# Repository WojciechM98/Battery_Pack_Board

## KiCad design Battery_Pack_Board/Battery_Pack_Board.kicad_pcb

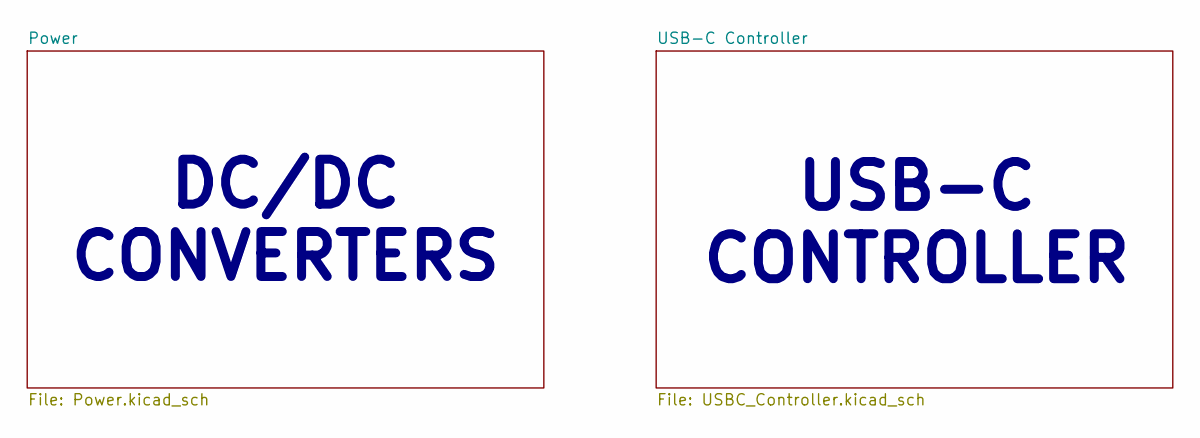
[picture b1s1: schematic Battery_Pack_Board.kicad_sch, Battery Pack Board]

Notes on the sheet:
DC/DC CONVERTERS
USB-C CONTROLLER

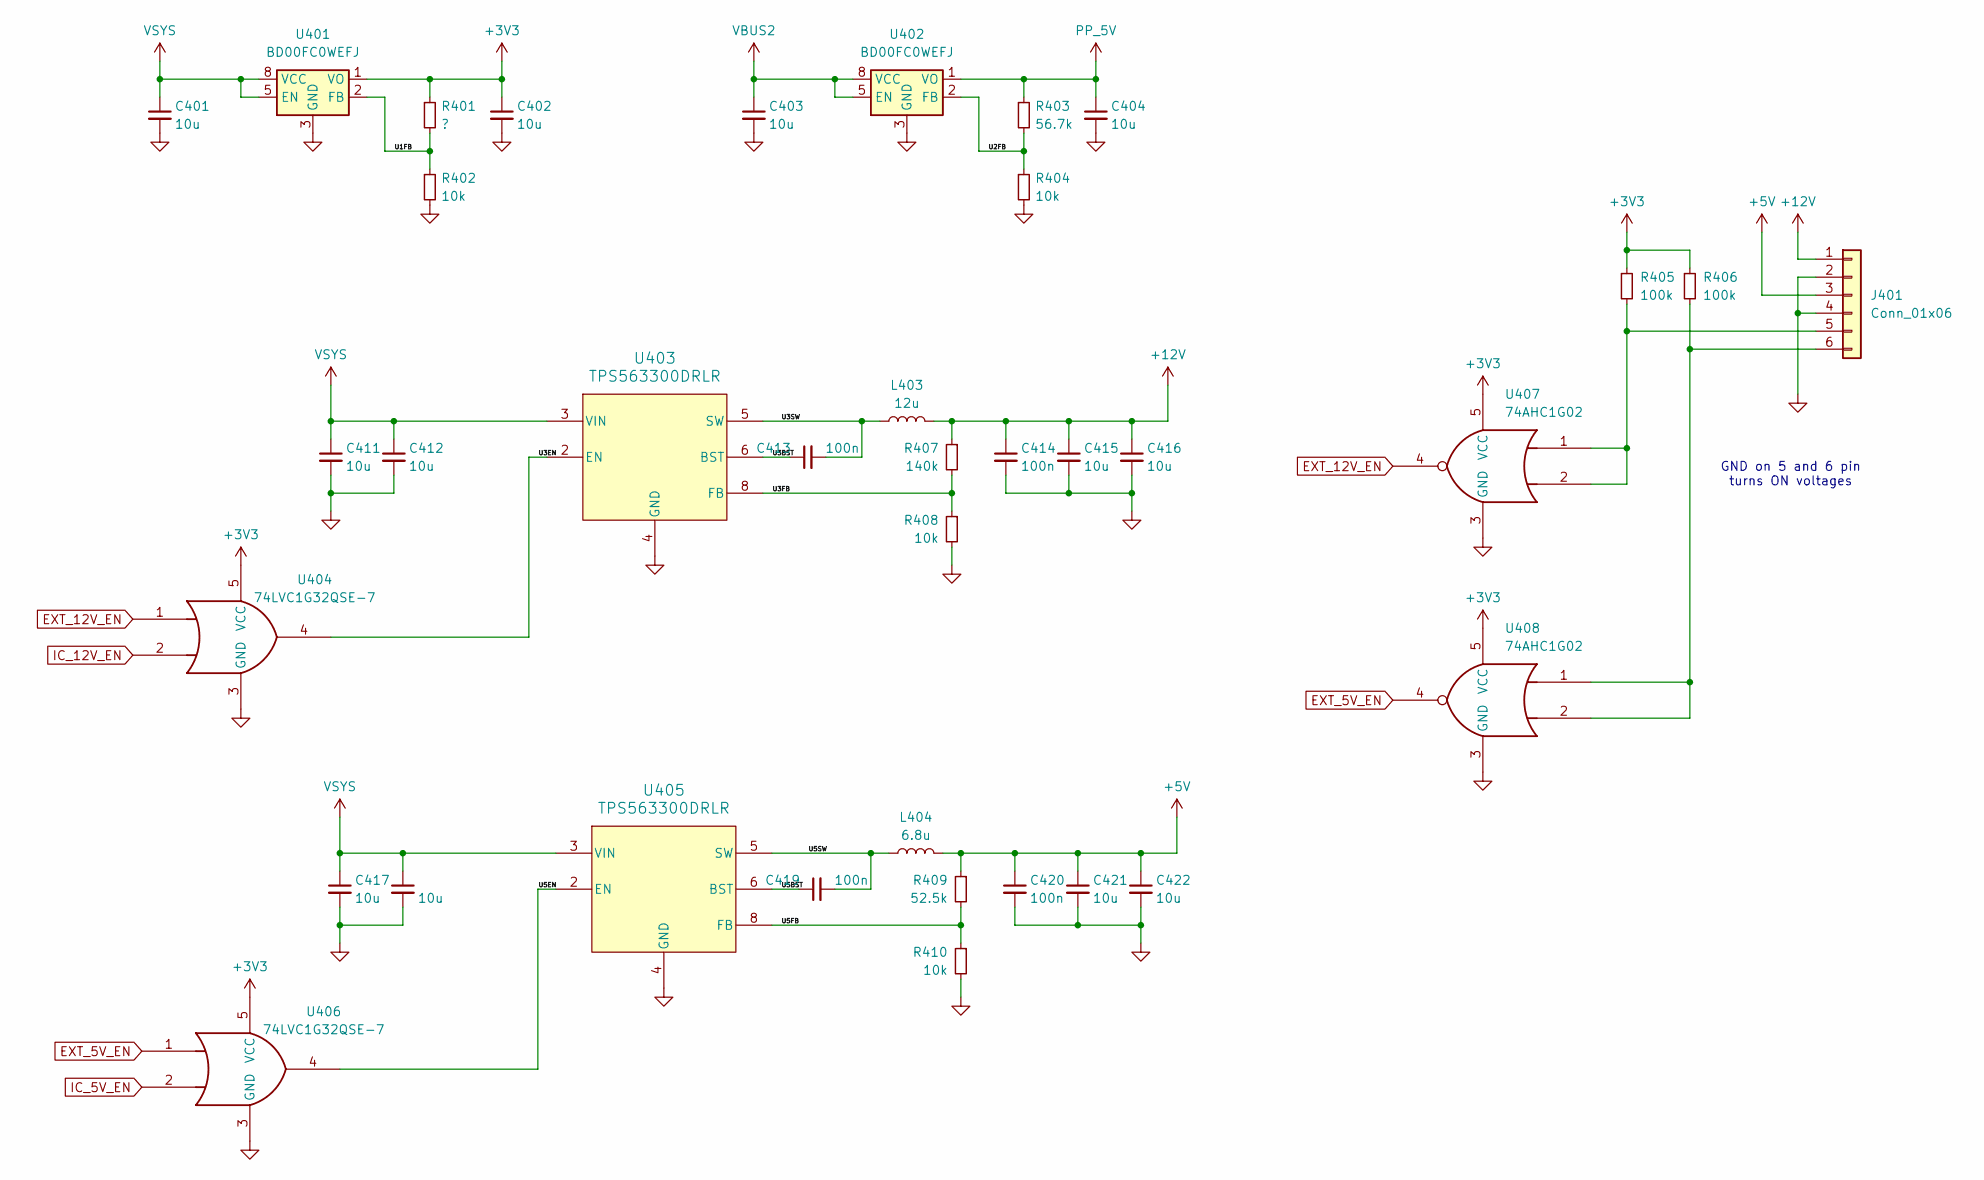
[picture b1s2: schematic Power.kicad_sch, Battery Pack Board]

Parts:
C401, C402, C403, C404, C411, C412, C415, C416, C417, C418, C421, C422: 10u; C_1206_3216Metric
C413, C414, C419, C420: 100n; C_0402_1005Metric
J401: Conn_01x06; 436500600
L403: 12u; SRR1050A
L404: 6.8u; SRP4020TA
R401: ?; R_0402_1005Metric
R402, R404, R408, R410: 10k; R_0402_1005Metric
R403: 56.7k; R_0402_1005Metric
R405, R406: 100k; R_0402_1005Metric
R407: 140k; R_0402_1005Metric
R409: 52.5k; R_0402_1005Metric
U401, U402: BD00FC0WEFJ; HTSOP-8-1EP_3.9x4.9mm_P1.27mm_EP2.4x3.2mm
U403, U405: TPS563300DRLR; SOT583_DRL
U404, U406: 74LVC1G32QSE-7; SOT65P210X110-5N_SOT-353
U407, U408: 74AHC1G02; SOT65P210X110-5N_SOT-353

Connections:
+3V3: C402.1, R401.1, R405.1, R406.1, U401.1 (VO), U404.5 (VCC), U406.5 (VCC), U407.5 (VCC), U408.5 (VCC); also elsewhere on the board
+5V: C420.1, C421.1, C422.1, J401.3, L404.2, R409.1; also elsewhere on the board
+12V: C414.1, C415.1, C416.1, J401.1, L403.2, R407.1; also elsewhere on the board
/Power/U1FB: R401.2, R402.1, U401.2 (FB)
/Power/U2FB: R403.2, R404.1, U402.2 (FB)
/Power/U3BST: C413.1, U403.6 (BST)
/Power/U3EN: U403.2 (EN), U404.4
/Power/U3FB: R407.2, R408.1, U403.8 (FB)
/Power/U3SW: C413.2, L403.1, U403.5 (SW)
/Power/U5BST: C419.1, U405.6 (BST)
/Power/U5EN: U405.2 (EN), U406.4
/Power/U5FB: R409.2, R410.1, U405.8 (FB)
/Power/U5SW: C419.2, L404.1, U405.5 (SW)
EXT_5V_EN: U406.1, U408.4
EXT_12V_EN: U404.1, U407.4
GND: C401.2, C402.2, C403.2, C404.2, C411.2, C412.2, C414.2, C415.2, C416.2, C417.2, C418.2, C420.2, C421.2, C422.2, J401.2, J401.4, R402.2, R404.2, R408.2, R410.2, U401.3 (GND), U401.9 (GND), U402.3 (GND), U402.9 (GND), U403.4 (GND), U404.3 (GND), U405.4 (GND), U406.3 (GND), U407.3 (GND), U408.3 (GND); also elsewhere on the board
IC_5V_EN: U406.2; also elsewhere on the board
IC_12V_EN: U404.2; also elsewhere on the board
unnamed: J401.5, R405.2, U407.1, U407.2
unnamed: J401.6, R406.2, U408.1, U408.2
PP_5V: C404.1, R403.1, U402.1 (VO); also elsewhere on the board
VBUS2: C403.1, U402.5 (EN), U402.8 (VCC); also elsewhere on the board
VSYS: C401.1, C411.1, C412.1, C417.1, C418.1, U401.5 (EN), U401.8 (VCC), U403.3 (VIN), U405.3 (VIN); also elsewhere on the board

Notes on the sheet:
GND on 5 and 6 pin turns ON voltages

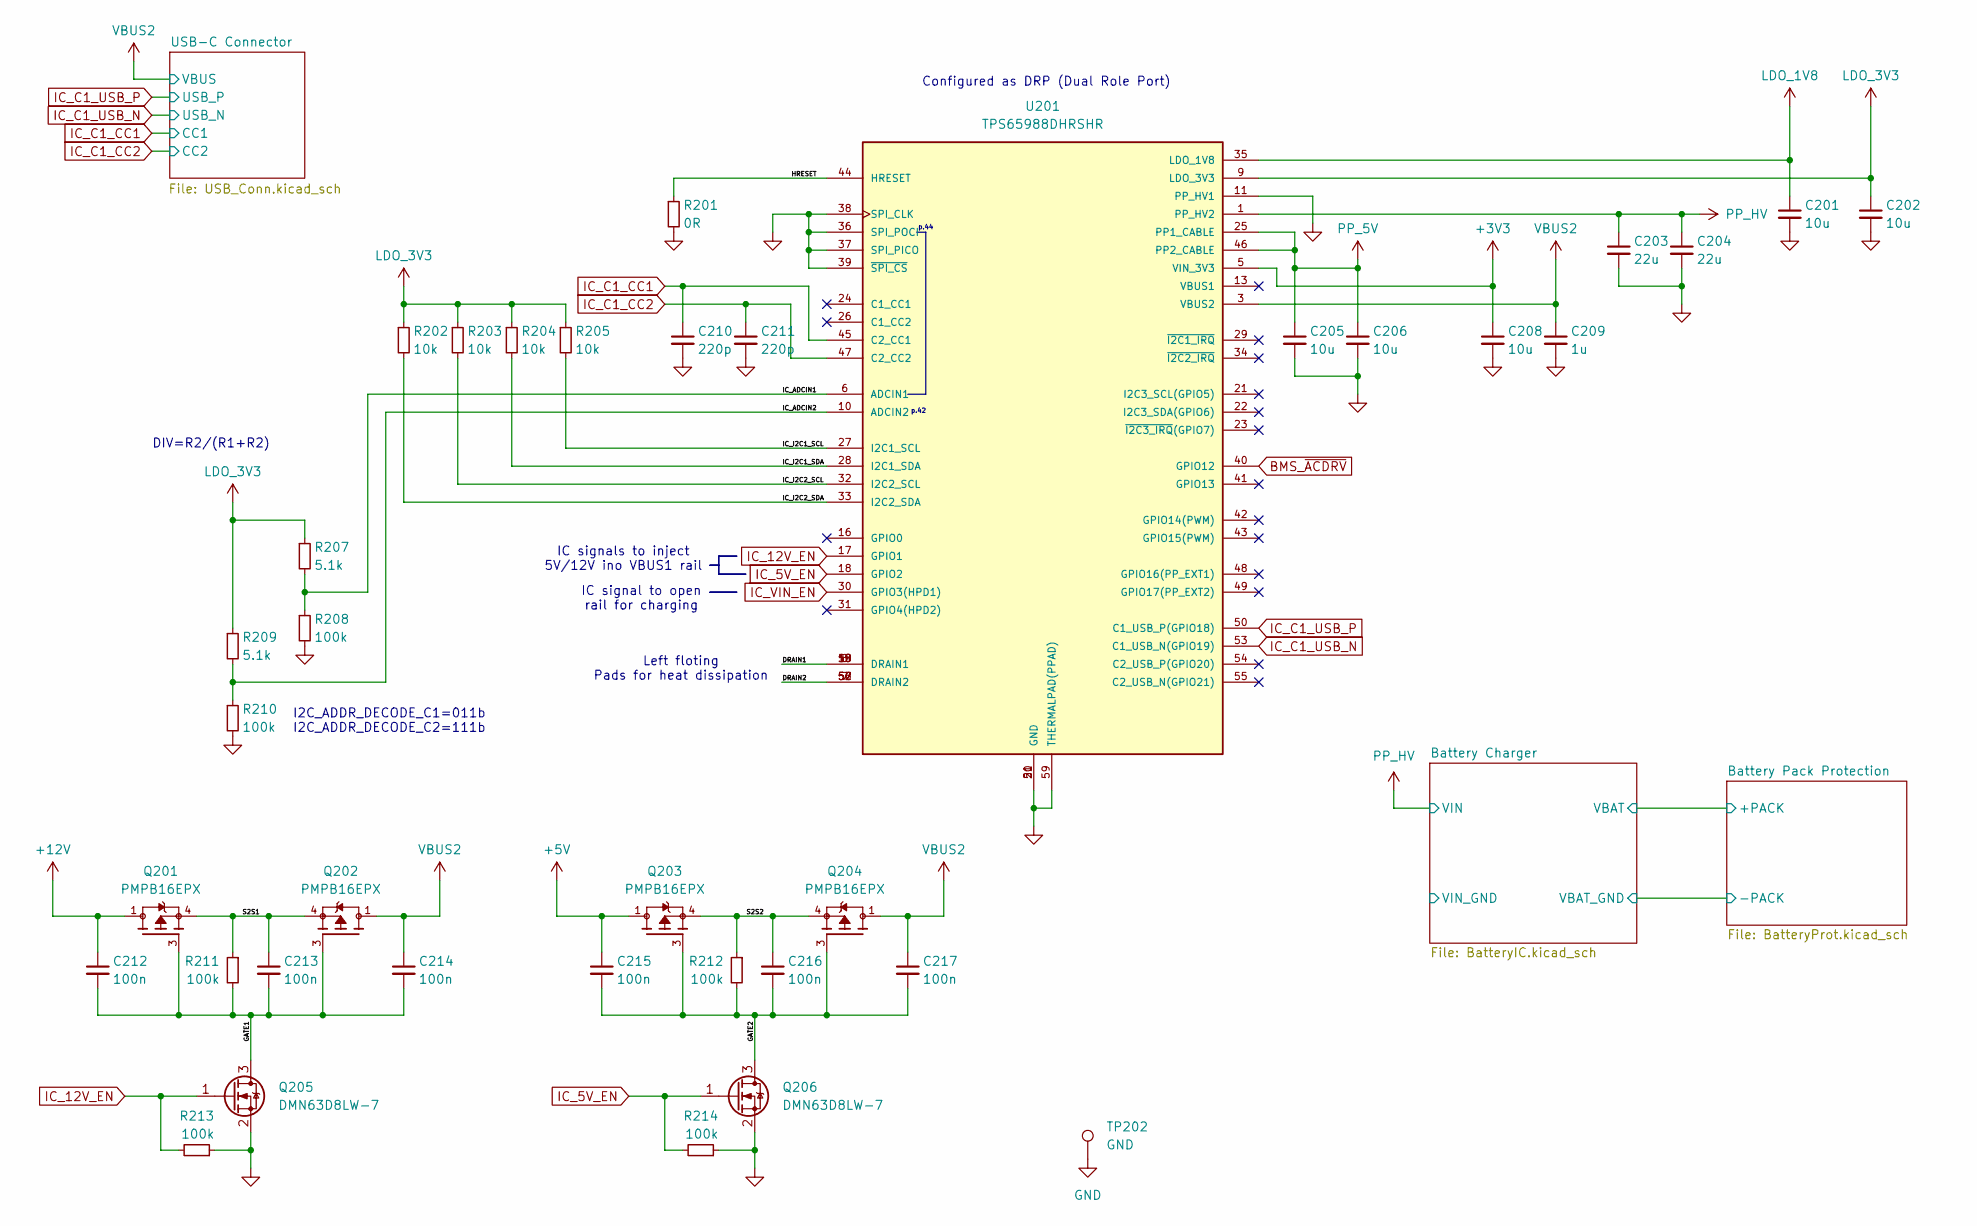
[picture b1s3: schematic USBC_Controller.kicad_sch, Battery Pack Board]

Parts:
C201, C202, C205, C206, C208: 10u; C_0402_1005Metric
C203, C204: 22u; C_0603_1608Metric
C209: 1u; C_0603_1608Metric
C210, C211: 220p; C_0402_1005Metric
C212, C213, C214, C215, C216, C217: 100n; C_0402_1005Metric
Q201, Q202, Q203, Q204: PMPB16EPX; PARTREV v.1
Q205, Q206: DMN63D8LW-7; SOT-323_SC-70
R201: 0R; R_0402_1005Metric
R202, R203, R204, R205: 10k; R_0402_1005Metric
R207, R209: 5.1k; R_0402_1005Metric
R208, R210, R211, R212, R213, R214: 100k; R_0402_1005Metric
TP202: GND; TestPoint_Pad_D2.0mm
U201: TPS65988DHRSHR; PARTREV AUGUST 2021

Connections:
+3V3: C208.1, U201.5 (VIN_3V3); also elsewhere on the board
+5V: C215.1, Q203.1, Q203.2, Q203.5, Q203.6, Q203.7; also elsewhere on the board
+12V: C212.1, Q201.1, Q201.2, Q201.5, Q201.6, Q201.7; also elsewhere on the board
/USB-C Controller/DRAIN1: U201.8 (DRAIN1), U201.15 (DRAIN1), U201.19 (DRAIN1), U201.58 (DRAIN1)
/USB-C Controller/DRAIN2: U201.7 (DRAIN2), U201.52 (DRAIN2), U201.56 (DRAIN2), U201.57 (DRAIN2)
/USB-C Controller/GATE1: C212.2, C213.2, C214.2, Q201.3, Q202.3, Q205.3 (D), R211.2
/USB-C Controller/GATE2: C215.2, C216.2, C217.2, Q203.3, Q204.3, Q206.3 (D), R212.2
/USB-C Controller/HRESET: R201.1, U201.44 (HRESET)
/USB-C Controller/IC_ADCIN1: R207.2, R208.1, U201.6 (ADCIN1)
/USB-C Controller/IC_ADCIN2: R209.2, R210.1, U201.10 (ADCIN2)
/USB-C Controller/IC_I2C1_SCL: R205.2, U201.27 (I2C1_SCL)
/USB-C Controller/IC_I2C1_SDA: R204.2, U201.28 (I2C1_SDA)
/USB-C Controller/IC_I2C2_SCL: R203.2, U201.32 (I2C2_SCL)
/USB-C Controller/IC_I2C2_SDA: R202.2, U201.33 (I2C2_SDA)
/USB-C Controller/S2S1: C213.1, Q201.4, Q201.8, Q202.4, Q202.8, R211.1
/USB-C Controller/S2S2: C216.1, Q203.4, Q203.8, Q204.4, Q204.8, R212.1
BMS_~ACDRV: U201.40 (GPIO12); also elsewhere on the board
GND: C201.2, C202.2, C203.2, C204.2, C205.2, C206.2, C208.2, C209.2, C210.2, C211.2, Q205.2 (S), Q206.2 (S), R201.2, R208.2, R210.2, R213.1, R214.1, TP202.1, U201.11 (PP_HV1), U201.12 (PP_HV1), U201.20 (GND), U201.36 (SPI_POCI), U201.37 (SPI_PICO), U201.38 (SPI_CLK), U201.39 (~SPI_CS), U201.51 (GND), U201.59 (THERMALPAD(PPAD)); also elsewhere on the board
IC_5V_EN: Q206.1 (G), R214.2, U201.18 (GPIO2); also elsewhere on the board
IC_12V_EN: Q205.1 (G), R213.2, U201.17 (GPIO1); also elsewhere on the board
IC_C1_CC1: C210.1, U201.45 (C2_CC1); also elsewhere on the board
IC_C1_CC2: C211.1, U201.47 (C2_CC2); also elsewhere on the board
IC_C1_USB_N: U201.53 (C1_USB_N(GPIO19)); also elsewhere on the board
IC_C1_USB_P: U201.50 (C1_USB_P(GPIO18)); also elsewhere on the board
IC_VIN_EN: U201.30 (GPIO3(HPD1)); also elsewhere on the board
LDO_1V8: C201.1, U201.35 (LDO_1V8)
LDO_3V3: C202.1, R202.1, R203.1, R204.1, R205.1, R207.1, R209.1, U201.9 (LDO_3V3)
PP_5V: C205.1, C206.1, U201.25 (PP1_CABLE), U201.46 (PP2_CABLE); also elsewhere on the board
PP_HV: C203.1, C204.1, U201.1 (PP_HV2), U201.2 (PP_HV2); also elsewhere on the board
VBUS2: C209.1, C214.1, C217.1, Q202.1, Q202.2, Q202.5, Q202.6, Q202.7, Q204.1, Q204.2, Q204.5, Q204.6, Q204.7, U201.3 (VBUS2), U201.4 (VBUS2); also elsewhere on the board

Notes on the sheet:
Left floting Pads for heat dissipation
DIV=R2/(R1+R2)
p.44
IC signals to inject 5V/12V ino VBUS1 rail
Configured as DRP (Dual Role Port)
p.42
IC signal to open rail for charging
I2C_ADDR_DECODE_C1=011b I2C_ADDR_DECODE_C2=111b

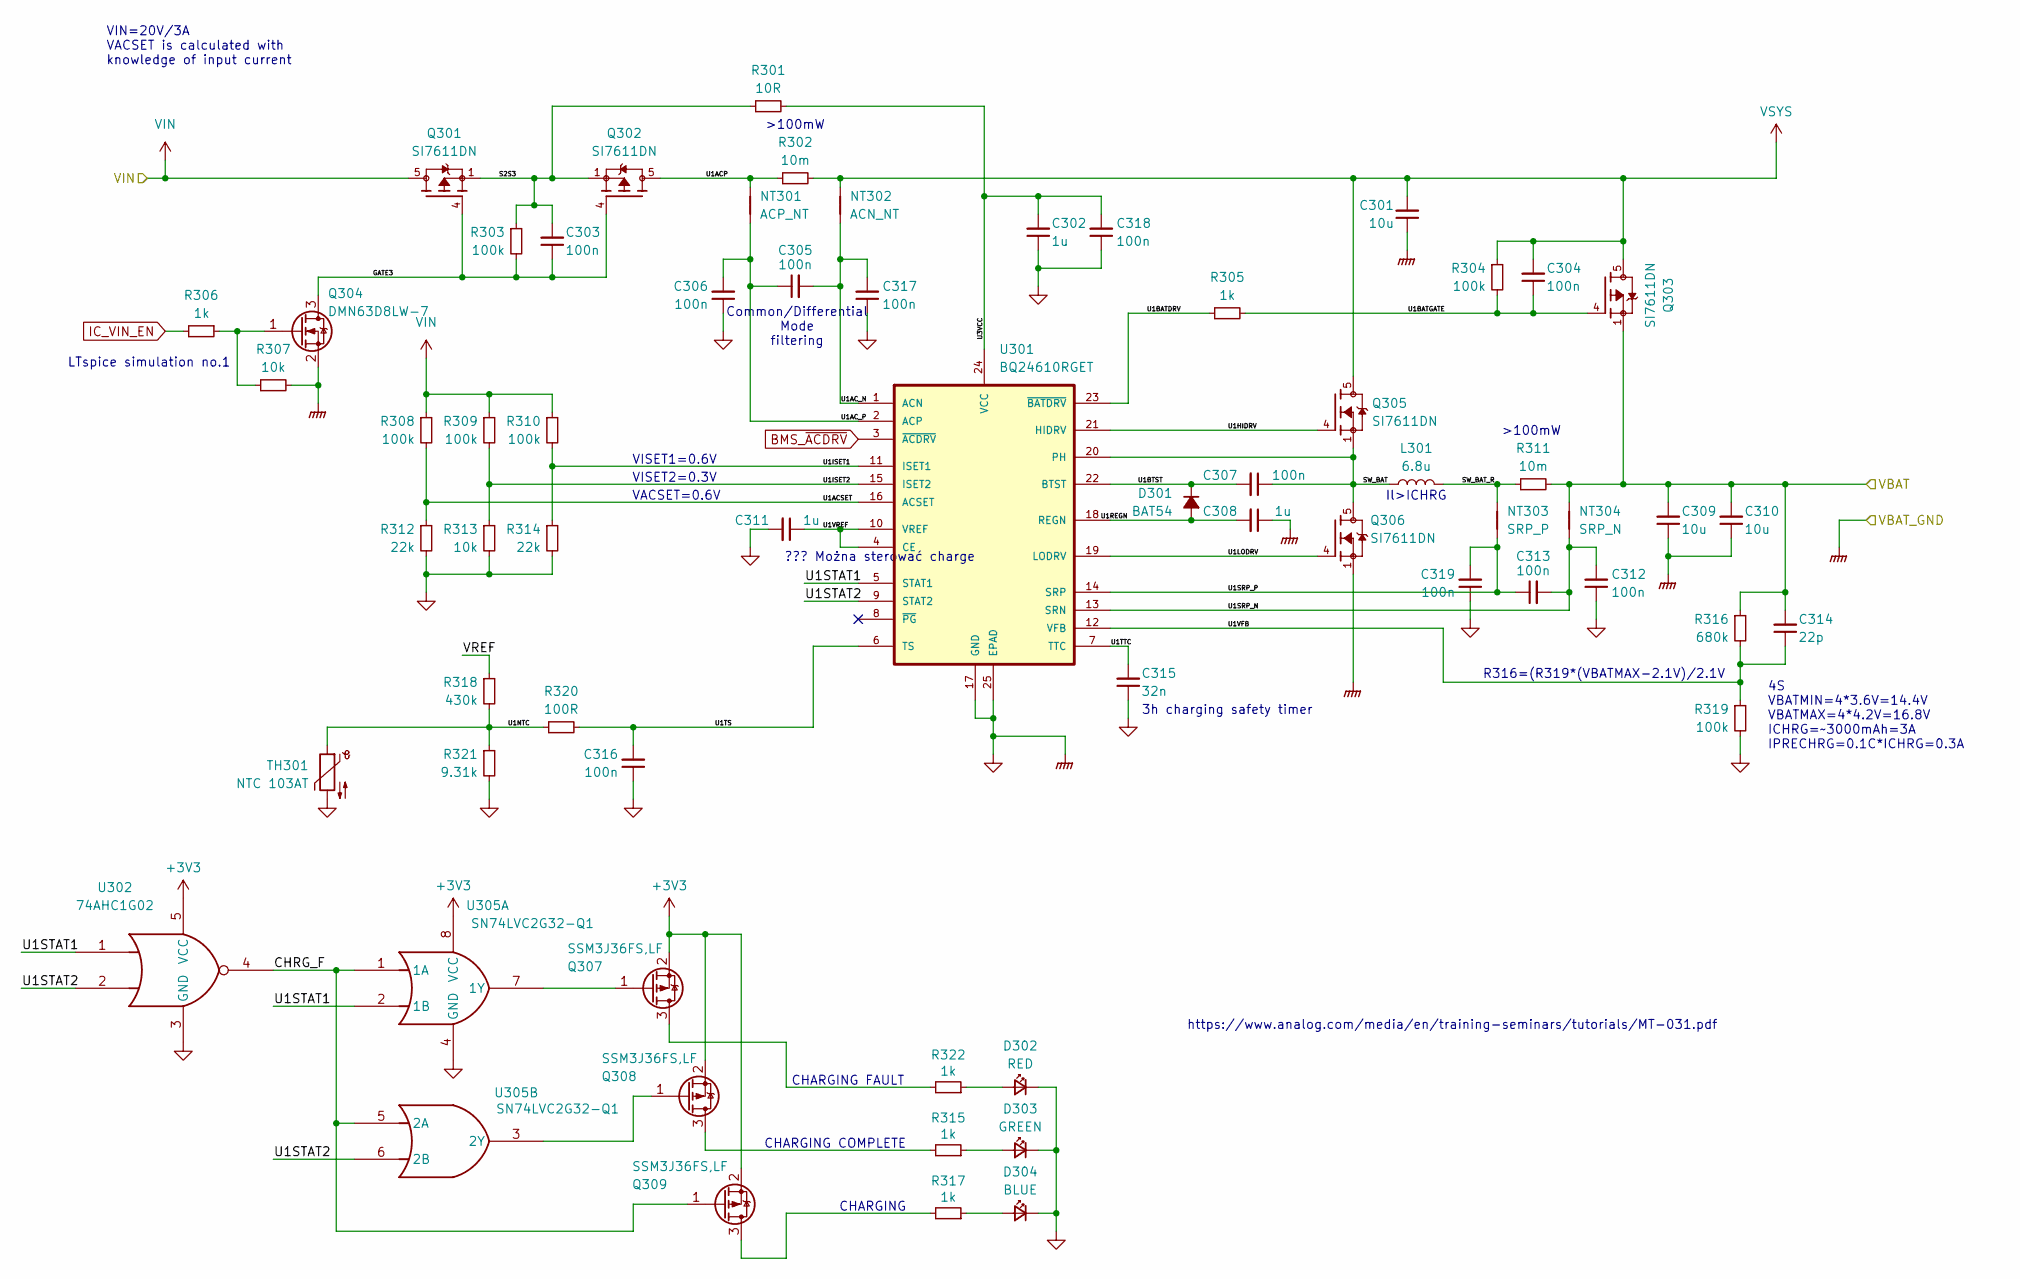
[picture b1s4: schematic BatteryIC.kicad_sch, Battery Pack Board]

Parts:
C301, C309, C310: 10u; C_1206_3216Metric
C302, C308, C311: 1u; C_0402_1005Metric
C303, C304, C305, C306, C307, C312, C313, C316, C317, C318, C319: 100n; C_0402_1005Metric
C314: 22p; C_0402_1005Metric
C315: 32n; C_0402_1005Metric
D301: BAT54; D_SOD-323F
D302: RED; LED_0603_1608Metric
D303: GREEN; LED_0603_1608Metric
D304: BLUE; LED_0603_1608Metric
L301: 6.8u; SRP4020TA
NT301: ACP_NT; NetTie_2_0,2mm
NT302: ACN_NT; NetTie_2_0,2mm
NT303: SRP_P; NetTie_2_0,2mm
NT304: SRP_N; NetTie_2_0,2mm
Q301, Q302, Q303: SI7611DN; VISHAY_SIS468DN-T1-GE3_SI7611DN-T1-GE3; PARTREV B
Q304: DMN63D8LW-7; SOT-323_SC-70
Q305, Q306: SI7611DN; VISHAY_SIS468DN-T1-GE3_SIS412DN-T1-GE3; PARTREV B
Q307, Q308, Q309: SSM3J36FS,LF; SOT-416
R301: 10R; R_0402_1005Metric
R302, R311: 10m; R_0805_2012Metric
R303, R304, R308, R309, R310, R319: 100k; R_0402_1005Metric
R305, R306, R315, R317, R322: 1k; R_0402_1005Metric
R307, R313: 10k; R_0402_1005Metric
R312, R314: 22k; R_0402_1005Metric
R316: 680k; R_0402_1005Metric
R318: 430k; R_0402_1005Metric
R320: 100R; R_0402_1005Metric
R321: 9.31k; R_0402_1005Metric
TH301: NTC 103AT; NTC_103AT
U301: BQ24610RGET; QFN50P400X400X100-25N
U302: 74AHC1G02; SOT65P210X110-5N_SOT-353
U305: SN74LVC2G32-Q1; SN74LVC2G32QDCURQ1

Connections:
+3V3: Q307.2 (S), Q308.2 (S), Q309.2 (S), U302.5 (VCC), U305.8 (VCC); also elsewhere on the board
/USB-C Controller/Battery Charger/CHRG_F: Q309.1 (G), U302.4, U305.1 (1A), U305.5 (2A)
/USB-C Controller/Battery Charger/GATE3: C303.1, Q301.4, Q302.4, Q304.3 (D), R303.2
/USB-C Controller/Battery Charger/S2S3: C303.2, Q301.1, Q301.2, Q301.3, Q302.1, Q302.2, Q302.3, R301.1, R303.1
/USB-C Controller/Battery Charger/SW_BAT: C307.1, L301.1, Q305.1, Q305.2, Q305.3, Q306.5, Q306.6, Q306.7, Q306.8, Q306.9, U301.20 (PH)
/USB-C Controller/Battery Charger/SW_BAT_R: L301.2, NT303.2, R311.1
/USB-C Controller/Battery Charger/U1ACP: NT301.2, Q302.5, Q302.6, Q302.7, Q302.8, Q302.9, R302.1
/USB-C Controller/Battery Charger/U1ACSET: R308.2, R312.1, U301.16 (ACSET)
/USB-C Controller/Battery Charger/U1AC_N: C305.2, C317.2, NT302.1, U301.1 (ACN)
/USB-C Controller/Battery Charger/U1AC_P: C305.1, C306.2, NT301.1, U301.2 (ACP)
/USB-C Controller/Battery Charger/U1BATDRV: R305.1, U301.23 (~BATDRV)
/USB-C Controller/Battery Charger/U1BATGATE: C304.1, Q303.4, R304.2, R305.2
/USB-C Controller/Battery Charger/U1BTST: C307.2, D301.1 (K), U301.22 (BTST)
/USB-C Controller/Battery Charger/U1HIDRV: Q305.4, U301.21 (HIDRV)
/USB-C Controller/Battery Charger/U1ISET1: R310.2, R314.1, U301.11 (ISET1)
/USB-C Controller/Battery Charger/U1ISET2: R309.2, R313.1, U301.15 (ISET2)
/USB-C Controller/Battery Charger/U1LODRV: Q306.4, U301.19 (LODRV)
/USB-C Controller/Battery Charger/U1NTC: R318.2, R320.1, R321.1, TH301.1
/USB-C Controller/Battery Charger/U1REGN: C308.2, D301.2 (A), U301.18 (REGN)
/USB-C Controller/Battery Charger/U1SRP_N: C312.2, C313.2, NT304.1, U301.13 (SRN)
/USB-C Controller/Battery Charger/U1SRP_P: C313.1, C319.2, NT303.1, U301.14 (SRP)
/USB-C Controller/Battery Charger/U1STAT1: U301.5 (STAT1), U302.1, U305.2 (1B)
/USB-C Controller/Battery Charger/U1STAT2: U301.9 (STAT2), U302.2, U305.6 (2B)
/USB-C Controller/Battery Charger/U1TS: C316.2, R320.2, U301.6 (TS)
/USB-C Controller/Battery Charger/U1TTC: C315.2, U301.7 (TTC)
/USB-C Controller/Battery Charger/U1VFB: C314.1, R316.2, R319.1, U301.12 (VFB)
/USB-C Controller/Battery Charger/U1VREF: C311.1, U301.4 (CE), U301.10 (VREF)
/USB-C Controller/Battery Charger/U3VCC: C302.2, C318.2, R301.2, U301.24 (VCC)
/USB-C Controller/Battery Charger/VBAT: C309.2, C310.2, C314.2, NT304.2, Q303.1, Q303.2, Q303.3, R311.2, R316.1; also elsewhere on the board
/USB-C Controller/Battery Charger/VREF: R318.1
BMS_~ACDRV: U301.3 (~ACDRV); also elsewhere on the board
GND: C301.1, C302.1, C306.1, C308.1, C309.1, C310.1, C311.2, C312.1, C315.1, C316.1, C317.1, C318.1, C319.1, D302.1 (K), D303.1 (K), D304.1 (K), Q304.2 (S), Q306.1, Q306.2, Q306.3, R307.2, R312.2, R313.2, R314.2, R319.2, R321.2, TH301.2, U301.17 (GND), U301.25 (EPAD), U302.3 (GND), U305.4 (GND); also elsewhere on the board
IC_VIN_EN: R306.2; also elsewhere on the board
unnamed: D302.2 (A), R322.1
unnamed: D303.2 (A), R315.1
unnamed: D304.2 (A), R317.1
unnamed: Q304.1 (G), R306.1, R307.1
unnamed: Q307.3 (D), R322.2
unnamed: Q307.1 (G), U305.7 (1Y)
unnamed: Q308.3 (D), R315.2
unnamed: Q308.1 (G), U305.3 (2Y)
unnamed: Q309.3 (D), R317.2
PP_HV: Q301.5, Q301.6, Q301.7, Q301.8, Q301.9, R308.1, R309.1, R310.1; also elsewhere on the board
VSYS: C301.2, C304.2, NT302.2, Q303.5, Q303.6, Q303.7, Q303.8, Q303.9, Q305.5, Q305.6, Q305.7, Q305.8, Q305.9, R302.2, R304.1; also elsewhere on the board

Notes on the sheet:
VISET2=0.3V
??? Można sterować charge
Il>ICHRG
>100mW
https://www.analog.com/media/en/training-seminars/tutorials/MT-031.pdf
3h charging safety timer
VISET1=0.6V
Common/Differential Mode filtering
LTspice simulation no.1
CHARGING COMPLETE
R316=(R319*(VBATMAX-2.1V)/2.1V
VIN=20V/3A VACSET is calculated with knowledge of input current
CHARGING
VACSET=0.6V
4S VBATMIN=4*3.6V=14.4V VBATMAX=4*4.2V=16.8V ICHRG=~3000mAh=3A IPRECHRG=0.1C*ICHRG=0.3A
CHARGING FAULT

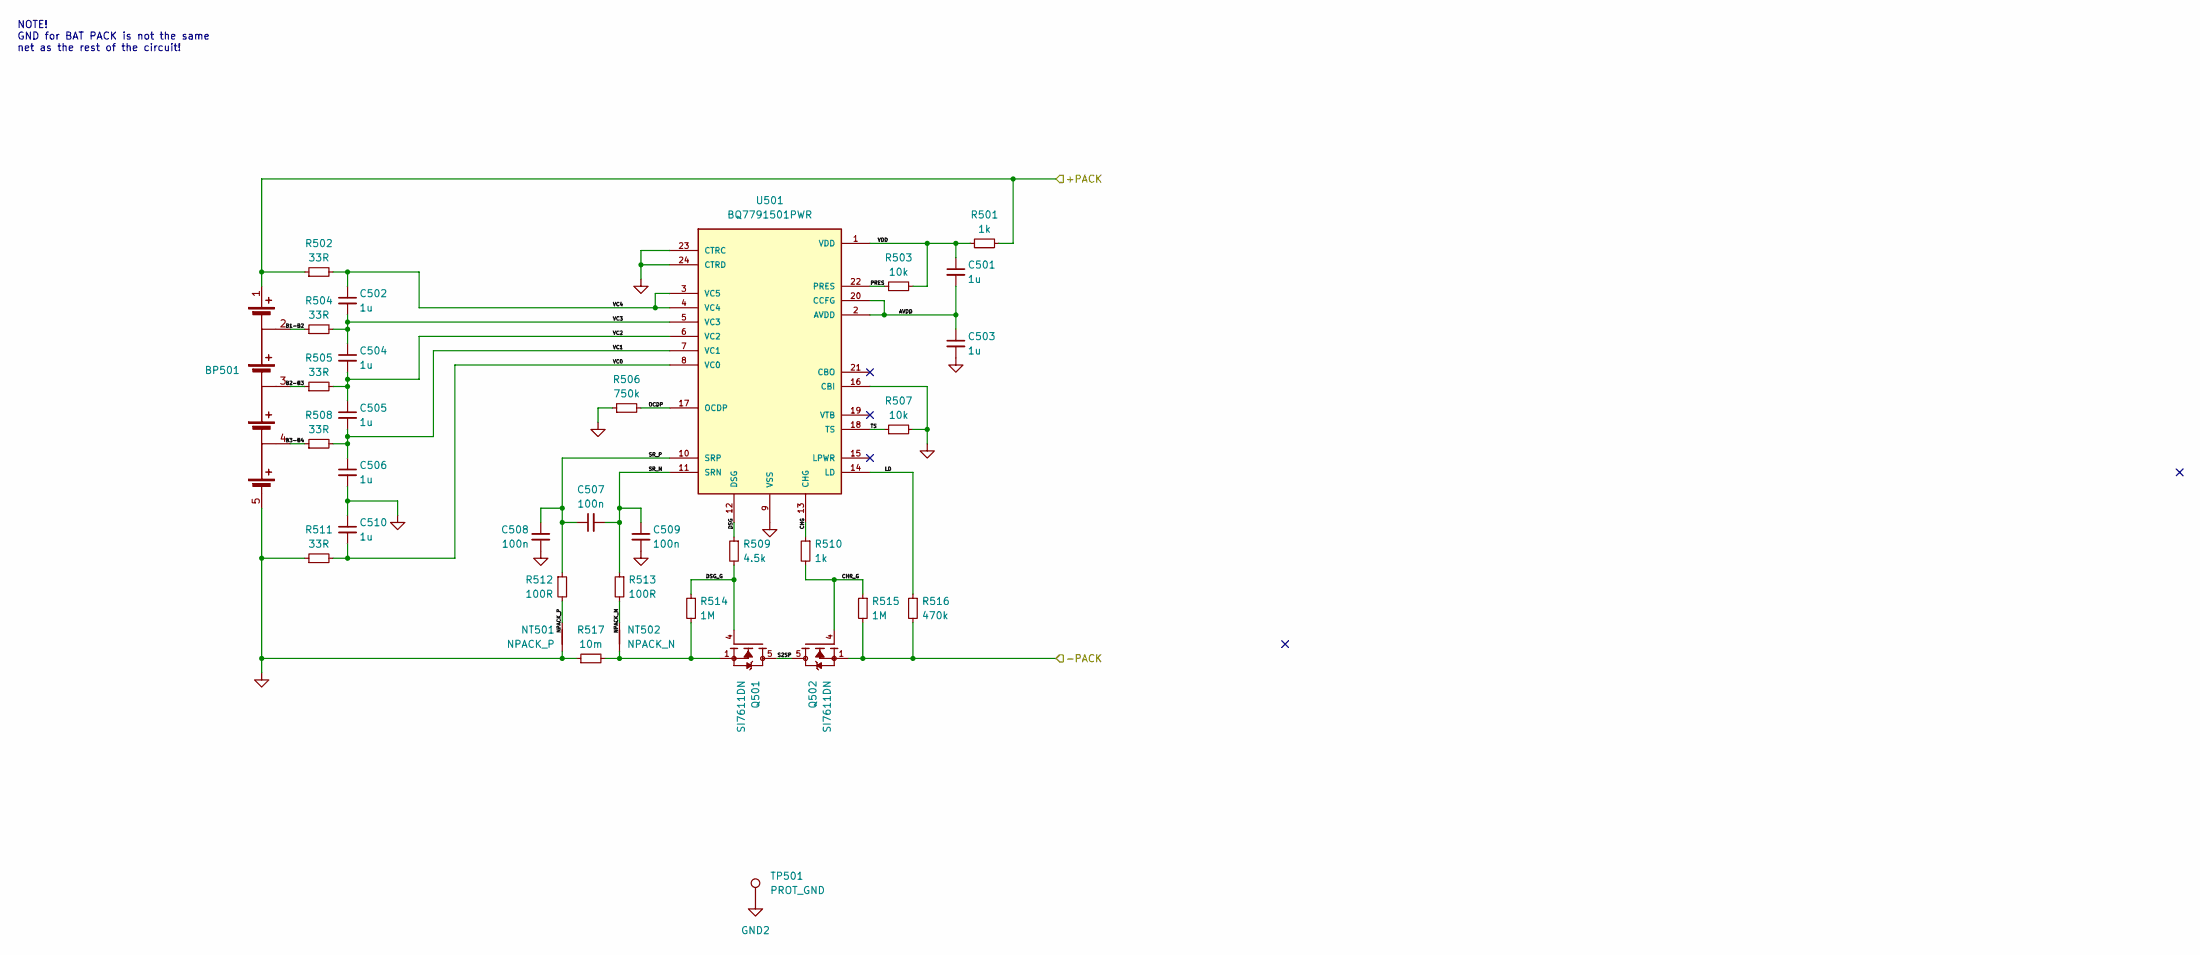
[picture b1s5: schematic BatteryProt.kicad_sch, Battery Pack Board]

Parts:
BP501: BatPack_4S
C501, C502, C503, C504, C505, C506, C510: 1u; C_0402_1005Metric
C507, C508, C509: 100n; C_0402_1005Metric
NT501: NPACK_P; NetTie_2_0,2mm
NT502: NPACK_N; NetTie_2_0,2mm
Q501, Q502: SI7611DN; VISHAY_SIS468DN-T1-GE3_SIS412DN-T1-GE3; PARTREV B
R501, R510: 1k; R_0402_1005Metric
R502, R504, R505, R508, R511: 33R; R_0402_1005Metric
R503, R507: 10k; R_0402_1005Metric
R506: 750k; R_0402_1005Metric
R509: 4.5k; R_0402_1005Metric
R512, R513: 100R; R_0402_1005Metric
R514, R515: 1M; R_0402_1005Metric
R516: 470k; R_0402_1005Metric
R517: 10m; R_0805_2012Metric
TP501: PROT_GND; TestPoint_Pad_D2.0mm
U501: BQ7791501PWR; SOP65P640X120-24N_BQ7791501PWR; PARTREV H

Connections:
/USB-C Controller/Battery Charger/VBAT: BP501.1, R501.2, R502.1; also elsewhere on the board
/USB-C Controller/Battery Pack Protection/AVDD: C501.2, C503.1, U501.2 (AVDD), U501.20 (CCFG)
/USB-C Controller/Battery Pack Protection/B1-B2: BP501.2, R504.1
/USB-C Controller/Battery Pack Protection/B2-B3: BP501.3, R505.1
/USB-C Controller/Battery Pack Protection/B3-B4: BP501.4, R508.1
/USB-C Controller/Battery Pack Protection/CHG: R510.1, U501.13 (CHG)
/USB-C Controller/Battery Pack Protection/CHR_G: Q502.4, R510.2, R515.1
/USB-C Controller/Battery Pack Protection/DSG: R509.1, U501.12 (DSG)
/USB-C Controller/Battery Pack Protection/DSG_G: Q501.4, R509.2, R514.1
/USB-C Controller/Battery Pack Protection/LD: R516.1, U501.14 (LD)
/USB-C Controller/Battery Pack Protection/NPACK_N: NT502.2, R513.2
/USB-C Controller/Battery Pack Protection/NPACK_P: NT501.2, R512.2
/USB-C Controller/Battery Pack Protection/OCDP: R506.2, U501.17 (OCDP)
/USB-C Controller/Battery Pack Protection/PRES: R503.1, U501.22 (PRES)
/USB-C Controller/Battery Pack Protection/S2SP: Q501.5, Q501.6, Q501.7, Q501.8, Q501.9, Q502.5, Q502.6, Q502.7, Q502.8, Q502.9
/USB-C Controller/Battery Pack Protection/SR_N: C507.2, C509.1, R513.1, U501.11 (SRN)
/USB-C Controller/Battery Pack Protection/SR_P: C507.1, C508.1, R512.1, U501.10 (SRP)
/USB-C Controller/Battery Pack Protection/TS: R507.1, U501.18 (TS)
/USB-C Controller/Battery Pack Protection/VC0: C510.2, R511.2, U501.8 (VC0)
/USB-C Controller/Battery Pack Protection/VC1: C505.2, C506.1, R508.2, U501.7 (VC1)
/USB-C Controller/Battery Pack Protection/VC2: C504.2, C505.1, R505.2, U501.6 (VC2)
/USB-C Controller/Battery Pack Protection/VC3: C502.2, C504.1, R504.2, U501.5 (VC3)
/USB-C Controller/Battery Pack Protection/VC4: C502.1, R502.2, U501.3 (VC5), U501.4 (VC4)
/USB-C Controller/Battery Pack Protection/VDD: C501.1, R501.1, R503.2, U501.1 (VDD)
GND: Q502.1, Q502.2, Q502.3, R515.2, R516.2; also elsewhere on the board
GND2: BP501.5, C503.2, C506.2, C508.2, C509.2, C510.1, NT501.1, R506.1, R507.2, R511.1, R517.1, TP501.1, U501.9 (VSS), U501.16 (CBI), U501.23 (CTRC), U501.24 (CTRD)
unnamed: NT502.1, Q501.1, Q501.2, Q501.3, R514.2, R517.2

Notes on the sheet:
NOTE! GND for BAT PACK is not the same net as the rest of the circuit!

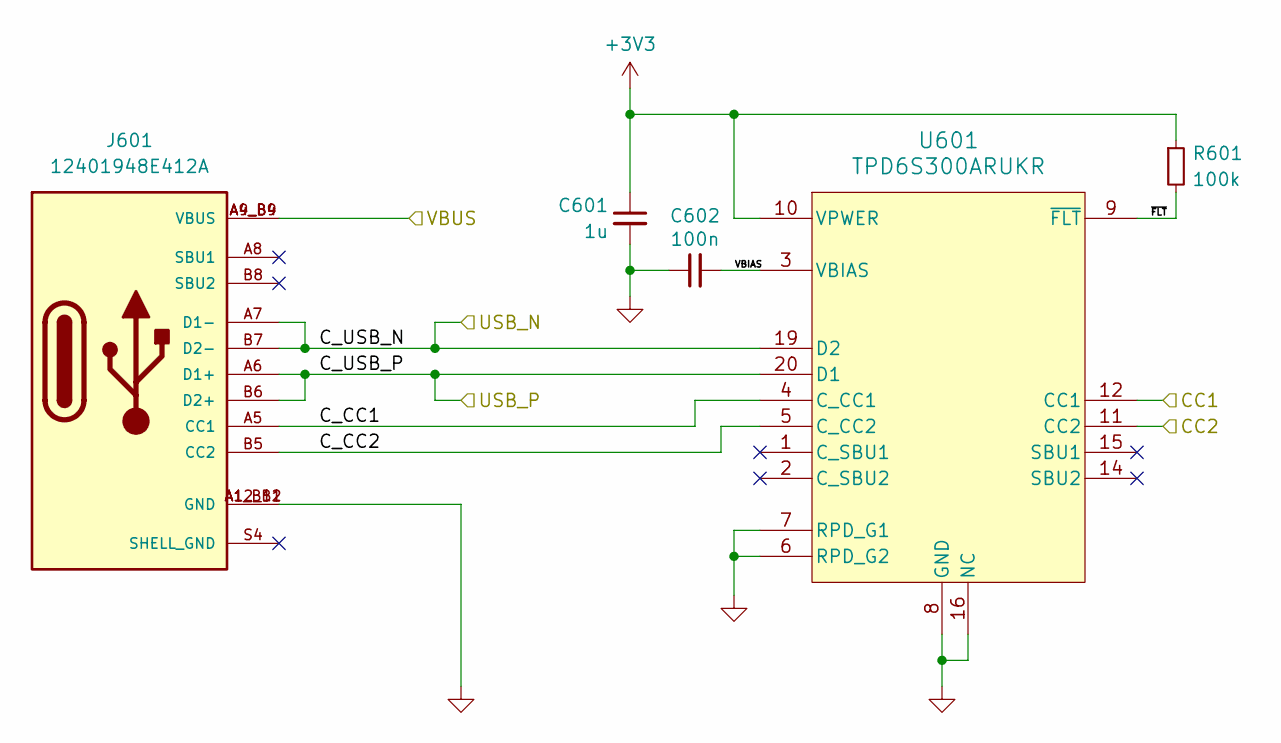
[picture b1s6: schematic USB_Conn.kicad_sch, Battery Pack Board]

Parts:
C601: 1u; C_0402_1005Metric
C602: 100n; C_0402_1005Metric
J601: 12401948E412A; AMPHENOL_12401948E412A; PARTREV 3
R601: 100k; R_0402_1005Metric
U601: TPD6S300ARUKR; WQFN20_RUK_TEX_TPD6S300ARUKR

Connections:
+3V3: C601.1, R601.1, U601.10 (VPWER); also elsewhere on the board
/USB-C Controller/USB-C Connector/C_CC1: J601.A5 (CC1), U601.4 (C_CC1)
/USB-C Controller/USB-C Connector/C_CC2: J601.B5 (CC2), U601.5 (C_CC2)
/USB-C Controller/USB-C Connector/VBIAS: C602.2, U601.3 (VBIAS)
/USB-C Controller/USB-C Connector/~FLT: R601.2, U601.9 (~FLT)
GND: C601.2, C602.1, J601.A1_B12 (GND), J601.A12_B1 (GND), U601.6 (RPD_G2), U601.7 (RPD_G1), U601.8 (GND), U601.13 (GND), U601.16 (NC), U601.17 (NC), U601.18 (GND), U601.21 (GND); also elsewhere on the board
IC_C1_CC1: U601.12 (CC1); also elsewhere on the board
IC_C1_CC2: U601.11 (CC2); also elsewhere on the board
IC_C1_USB_N: J601.A7 (D1-), J601.B7 (D2-), U601.19 (D2); also elsewhere on the board
IC_C1_USB_P: J601.A6 (D1+), J601.B6 (D2+), U601.20 (D1); also elsewhere on the board
VBUS2: J601.A4_B9 (VBUS), J601.A9_B4 (VBUS); also elsewhere on the board

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
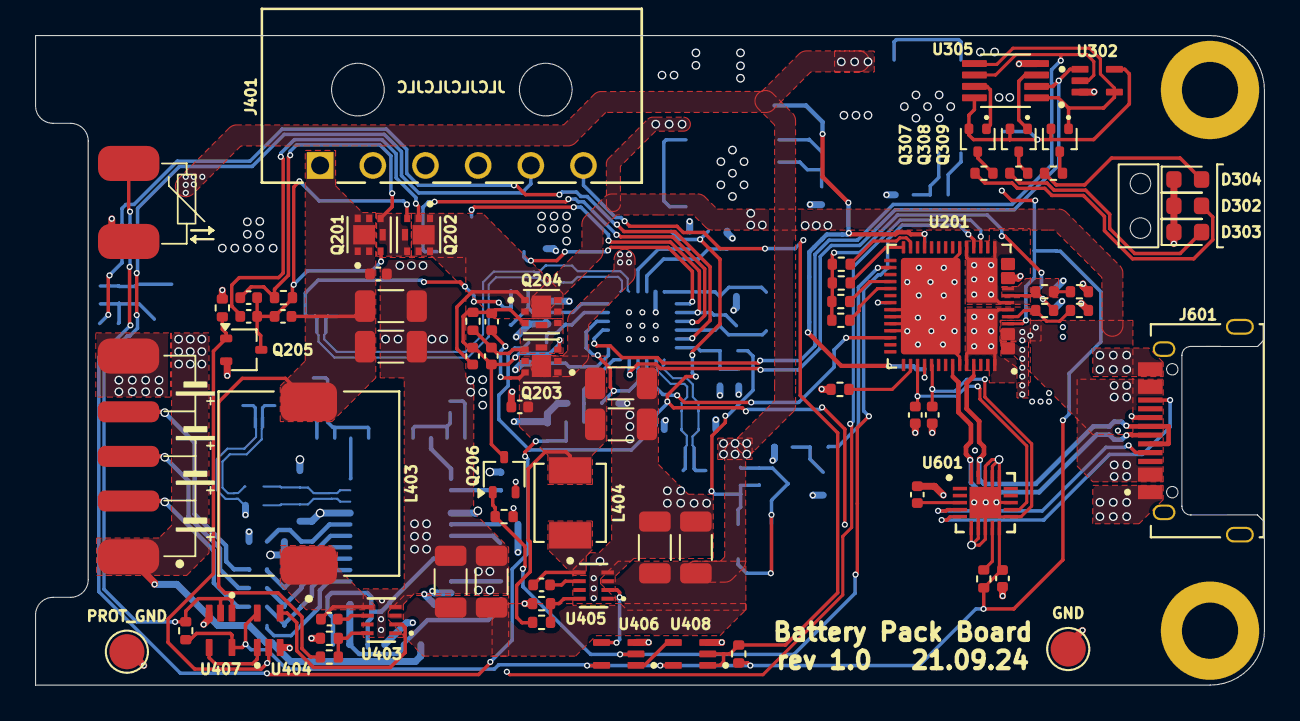
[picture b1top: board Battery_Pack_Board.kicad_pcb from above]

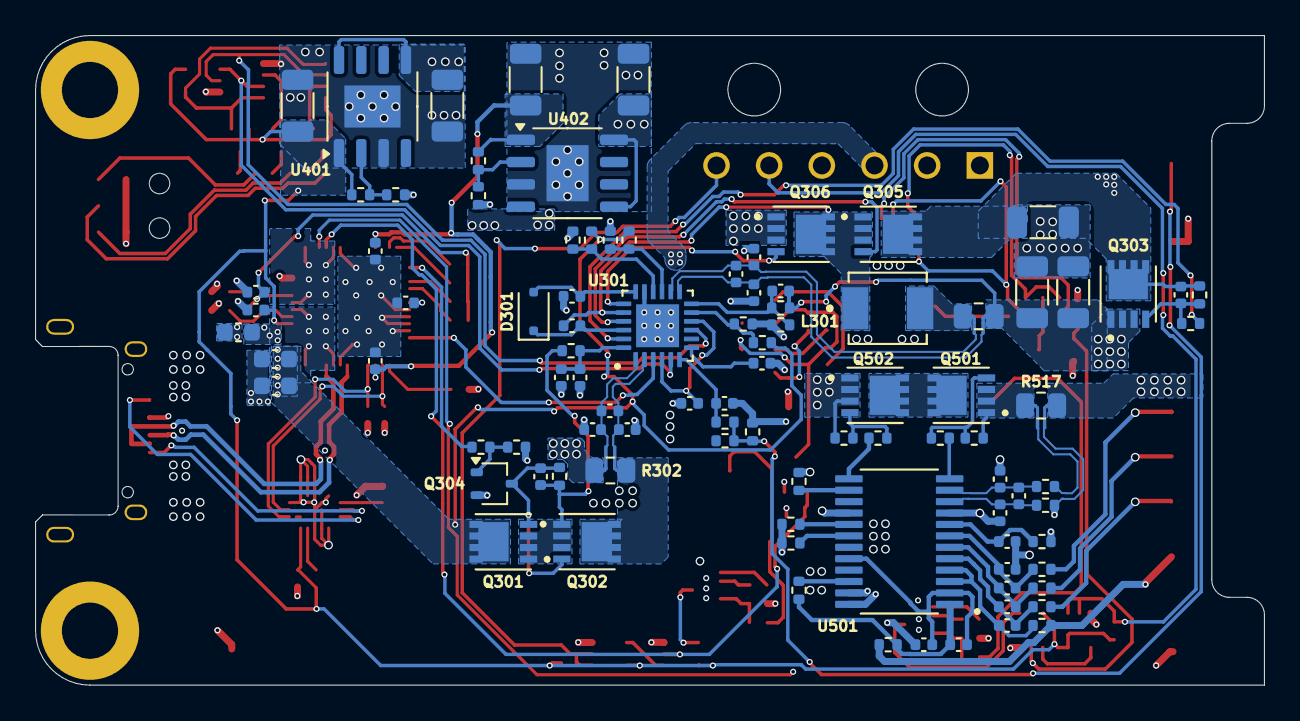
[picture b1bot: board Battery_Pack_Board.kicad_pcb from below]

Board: 4 copper layers, 70.0 x 37.0 mm, 176 parts (101 on the bottom side), 111 nets.

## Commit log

2024-09-21 First developer version rev 1.0
